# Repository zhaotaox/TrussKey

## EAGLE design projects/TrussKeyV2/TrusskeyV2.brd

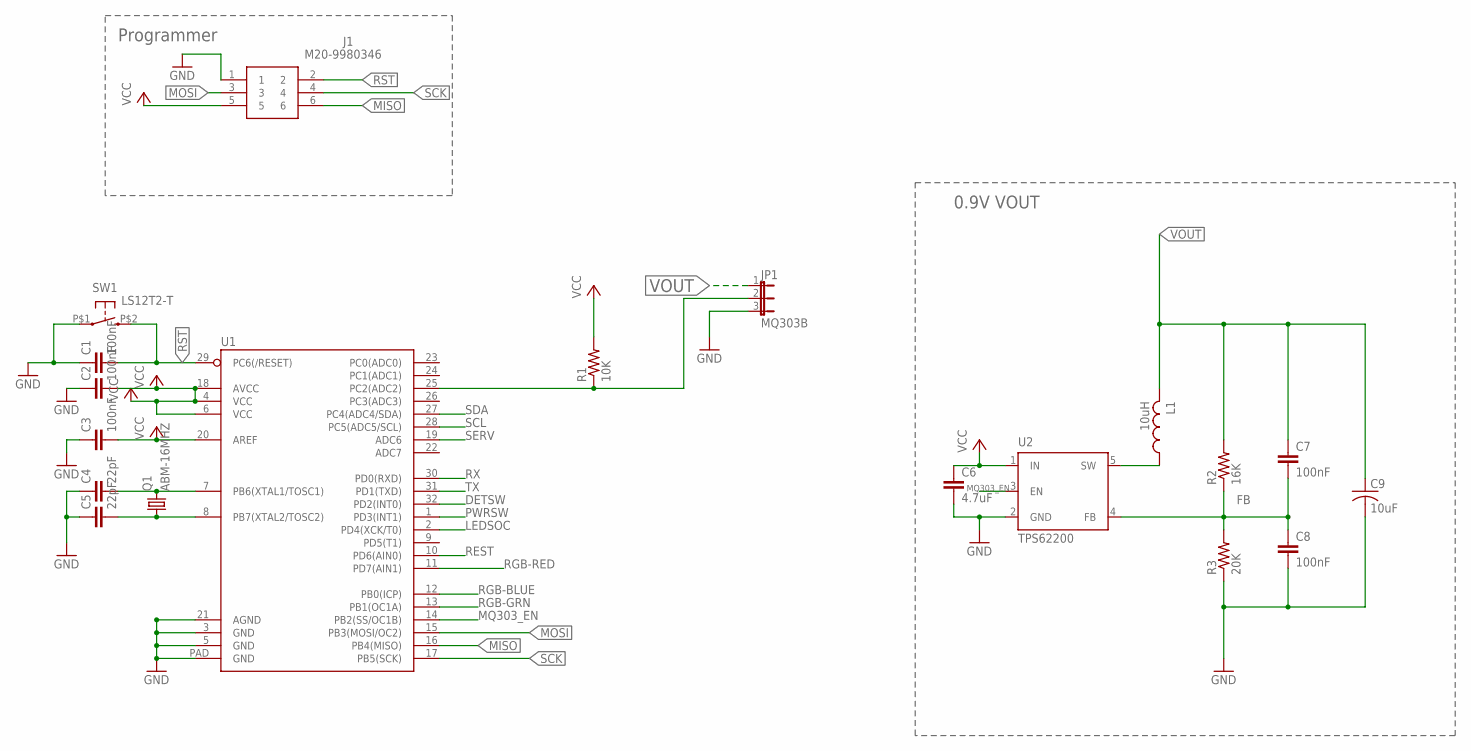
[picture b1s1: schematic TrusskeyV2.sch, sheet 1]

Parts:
C1, C2, C3: 100nF; C0603
C4, C5: 22pF; C0603
C6: 4.7uF; C0402
C7, C8: 100nF; C0402
C9: 10uF; C0805K
J1: M20-9980346; HDRV6W64P254_2X3_762X508X868P
JP1: MQ303B; JP2
L1: 10uH; L2825P
Q1: ABM-16MHZ
R1: 10K; R0402
R2: 16K; R0402
R3: 20K; R0402
SW1: LS12T2-T
U1: ATMEGA328P_MLFMLF32; MLF32-PAD
U2: TPS62200

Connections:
DETSW: U1.32 (PD2(INT0)); also elsewhere on the board
FB: C7.2, C8.1, R2.1, R3.2, U2.4 (FB)
GND: C1.1, C2.1, C3.1, C4.1, C5.1, C6.2, C8.2, C9.2, J1.1, JP1.3, R3.1, SW1.P$1 (S1), U1.3 (GND), U1.5 (GND), U1.21 (AGND), U1.PAD (GND), U2.2 (GND); also elsewhere on the board
LEDSOC: U1.2 (PD4(XCK/T0))
MISO: J1.6, U1.16 (PB4(MISO))
MOSI: J1.3, U1.15 (PB3(MOSI/OC2))
MQ303_EN: U1.14 (PB2(SS/OC1B)), U2.3 (EN)
unnamed: C5.2, Q1.P$1 (1), U1.8 (PB7(XTAL2/TOSC2))
unnamed: C4.2, Q1.P$2 (2), U1.7 (PB6(XTAL1/TOSC1))
unnamed: JP1.2, R1.1, U1.25 (PC2(ADC2))
PWRSW: U1.1 (PD3(INT1)); also elsewhere on the board
REST: U1.10 (PD6(AIN0)); also elsewhere on the board
RGB-BLUE: U1.12 (PB0(ICP)); also elsewhere on the board
RGB-GRN: U1.13 (PB1(OC1A)); also elsewhere on the board
RGB-RED: U1.11 (PD7(AIN1)); also elsewhere on the board
RST: C1.2, J1.2, SW1.P$2 (S2), U1.29 (PC6(/RESET))
RX: U1.30 (PD0(RXD)); also elsewhere on the board
SCK: J1.4, U1.17 (PB5(SCK))
SCL: U1.28 (PC5(ADC5/SCL)); also elsewhere on the board
SDA: U1.27 (PC4(ADC4/SDA)); also elsewhere on the board
SERV: U1.19 (ADC6); also elsewhere on the board
SW: L1.1, U2.5 (SW)
TX: U1.31 (PD1(TXD)); also elsewhere on the board
VCC: C2.2, C3.2, C6.1, J1.5, R1.2, U1.4 (VCC), U1.6 (VCC), U1.18 (AVCC), U1.20 (AREF), U2.1 (IN); also elsewhere on the board
VOUT: C7.1, C9.1, JP1.1, L1.2, R2.2

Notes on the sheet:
0.9V VOUT
Programmer

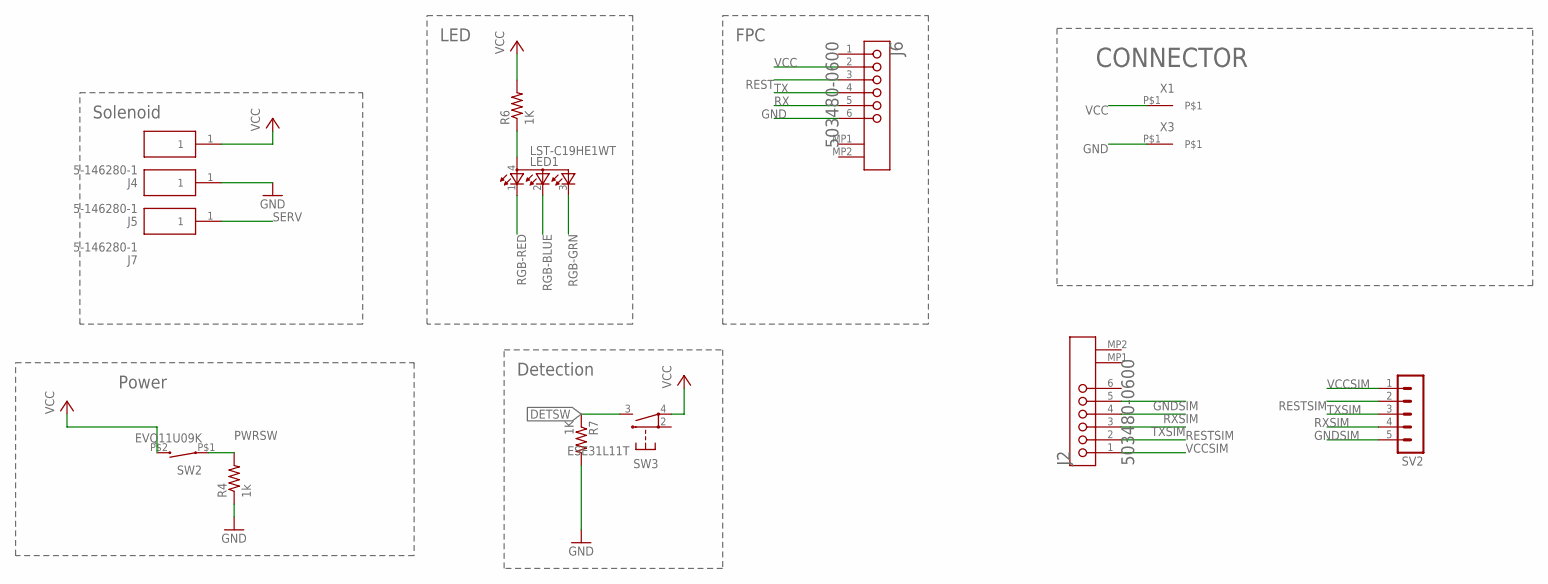
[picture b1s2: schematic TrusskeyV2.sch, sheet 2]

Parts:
J2, J6: MOLEX_503480-0600MOLEX_503480-0600_0_0; MOLEX_503480-0600_0
J4, J5, J7: 5-146280-1; HDRV1W67P0X254_1X1_213X234X821
LED1: LST-C19HE1WT
R4: 1k; R0402
R6, R7: 1K; R0402
SV2: MA05-1
SW2: EVQ11U09K; EVQ11U-09K
SW3: ESE31L11T; SWITCH
X1, X3: CON-1PIN

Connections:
DETSW: R7.1, SW3.3 (1); also elsewhere on the board
GND: J5.1, J6.6, R4.1, R7.2, X3.P$1; also elsewhere on the board
GNDSIM: J2.5, SV2.5
unnamed: LED1.4 (A), R6.1
PWRSW: R4.2, SW2.P$1 (1); also elsewhere on the board
REST: J6.3; also elsewhere on the board
RESTSIM: J2.2, SV2.2
RGB-BLUE: LED1.2 (CGREEN); also elsewhere on the board
RGB-GRN: LED1.3 (CBLUE); also elsewhere on the board
RGB-RED: LED1.1 (CRED); also elsewhere on the board
RX: J6.5; also elsewhere on the board
RXSIM: J2.4, SV2.4
SERV: J7.1; also elsewhere on the board
TX: J6.4; also elsewhere on the board
TXSIM: J2.3, SV2.3
VCC: J4.1, J6.2, R6.2, SW2.P$2 (2), SW3.4 (C3), X1.P$1; also elsewhere on the board
VCCSIM: J2.1, SV2.1

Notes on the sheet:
Solenoid
Power
LED
FPC
Detection
CONNECTOR

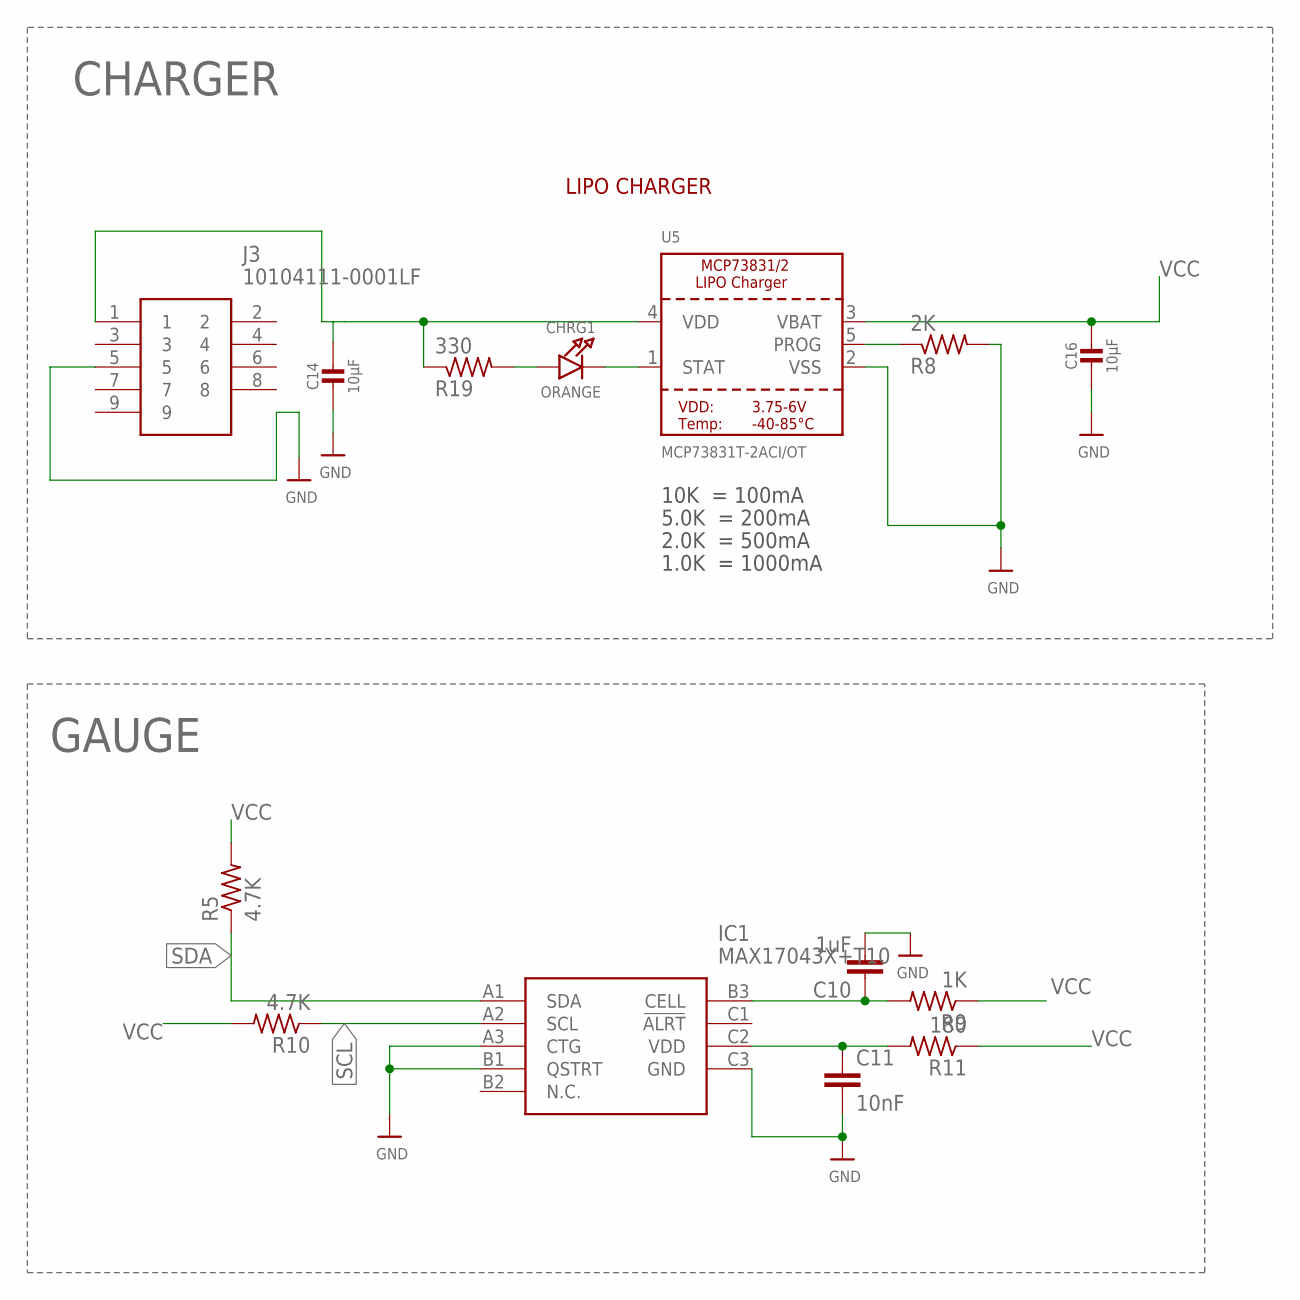
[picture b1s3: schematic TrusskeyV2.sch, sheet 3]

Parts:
C10: 1uF; C0603
C11: 10nF; C0603
C14, C16: 10µF; 0805-NO
CHRG1: ORANGE; CHIPLED_0805_NOOUTLINE
IC1: MAX17043X+T10; BGA9C40P3X3_160X142X69
J3: 10104111-0001LF; 101041110001LF
R5, R10: 4.7K; R0402
R8: 2K; R0402
R9: 1K; R0402
R11: 180; R0402
R19: 330; R0402
U5: MCP73831T-2ACI/OT; SOT23-5

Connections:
GND: C10.2, C11.2, C14.2, C16.2, IC1.A3 (CTG), IC1.B1 (QSTRT), IC1.C3 (GND), J3.5, R8.2, U5.2 (VSS); also elsewhere on the board
unnamed: C11.1, IC1.C2 (VDD), R11.2
unnamed: C10.1, IC1.B3 (CELL), R9.2
unnamed: R8.1, U5.5 (PROG)
unnamed: CHRG1.A, R19.2
unnamed: CHRG1.C, U5.1 (STAT)
SCL: IC1.A2 (SCL), R10.1; also elsewhere on the board
SDA: IC1.A1 (SDA), R5.1; also elsewhere on the board
VBUS2: C14.1, J3.1, R19.1, U5.4 (VDD)
VCC: C16.1, R5.2, R9.1, R10.2, R11.1, U5.3 (VBAT); also elsewhere on the board

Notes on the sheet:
10K = 100mA
5.0K = 200mA
2.0K = 500mA
1.0K = 1000mA
LIPO CHARGER
CHARGER
GAUGE

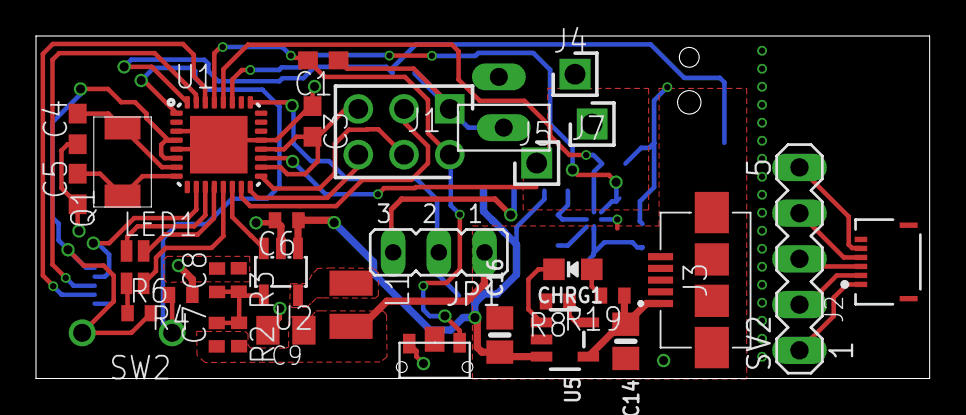
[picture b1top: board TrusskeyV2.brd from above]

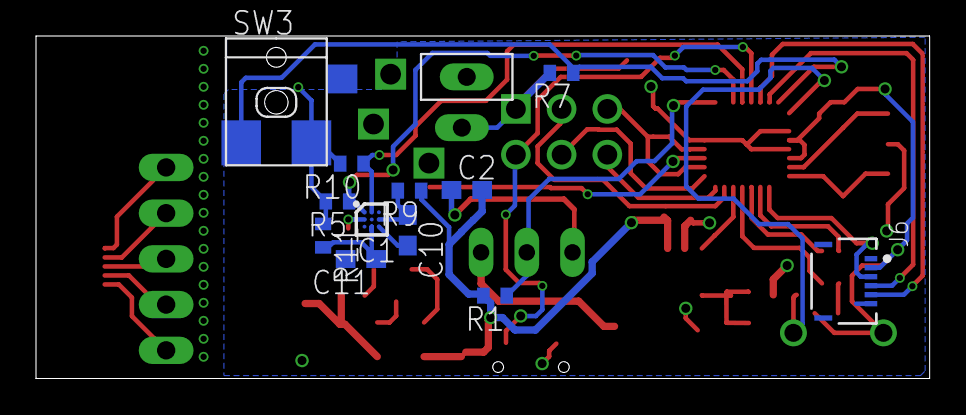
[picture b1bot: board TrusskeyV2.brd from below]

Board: 4 copper layers, 49.6 x 19.0 mm, 47 parts (13 on the bottom side), 36 nets.

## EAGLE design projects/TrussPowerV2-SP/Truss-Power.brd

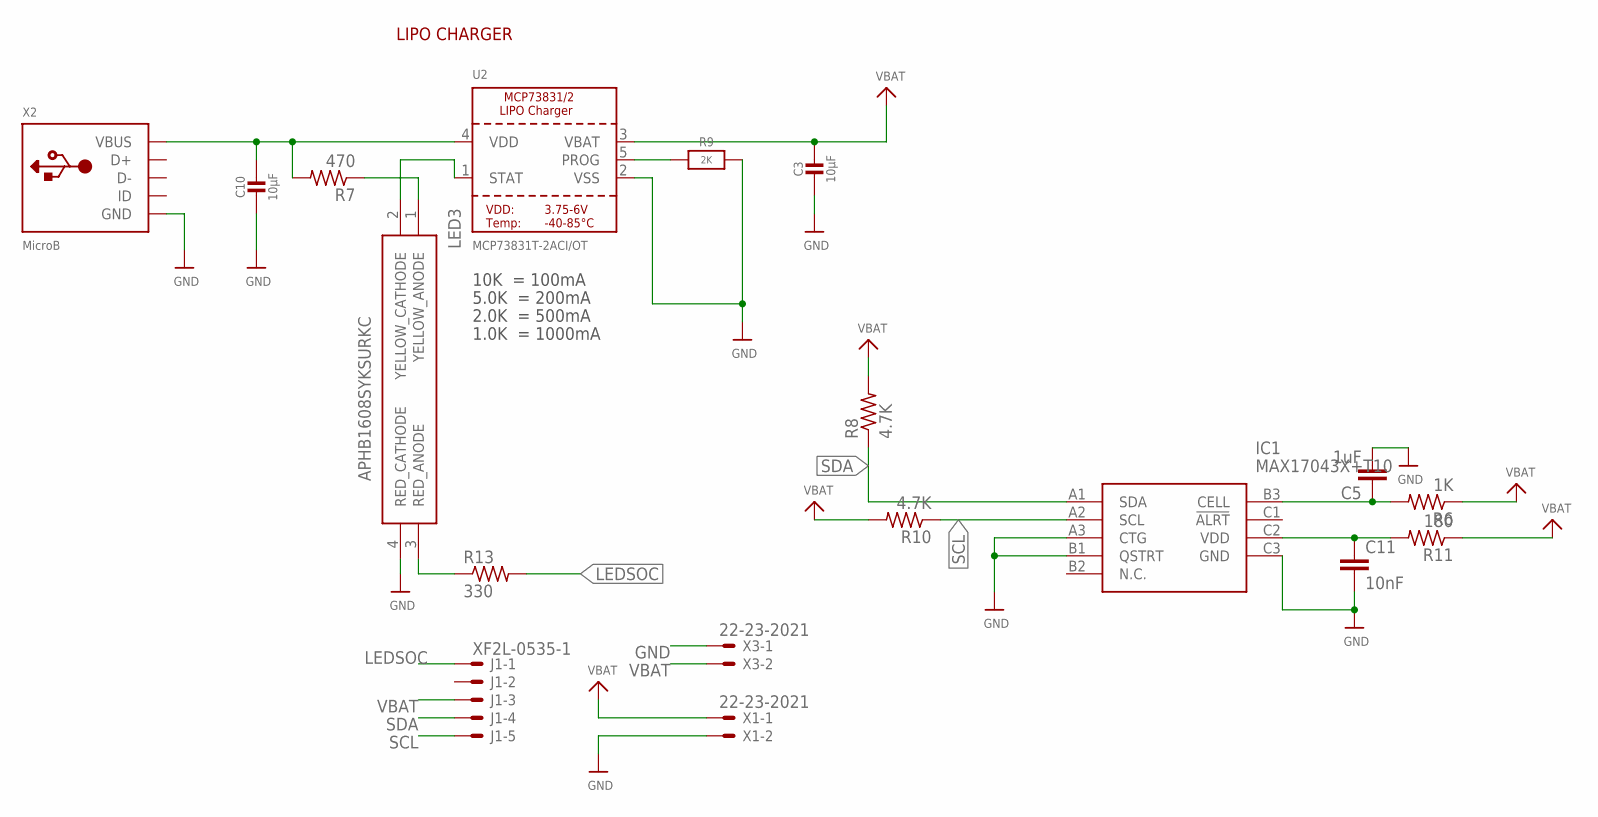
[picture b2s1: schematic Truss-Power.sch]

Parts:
C3, C10: 10µF; 0805-NO
C5: 1uF; C0603
C11: 10nF; C0603
IC1: MAX17043X+T10; BGA9C40P3X3_160X142X69
J1: XF2L-0535-1
LED3: APHB1608SYKSURKC; APHB1608ZGSURKC
R6: 1K; R0402
R7: 470; R0402
R8, R10: 4.7K; R0402
R9: 2K; 0805-NO
R11: 180; R0402
R13: 330; R0402
U2: MCP73831T-2ACI/OT; SOT23-5
X1, X3: 22-23-2021
X2: MicroB; 4UCONN_20329

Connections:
GND: C3.2, C5.2, C10.2, C11.2, IC1.A3 (CTG), IC1.B1 (QSTRT), IC1.C3 (GND), LED3.4 (RED_CATHODE), R9.2, U2.2 (VSS), X1.2, X2.BASE@1 (GND), X2.BASE@2 (GND), X2.GND, X2.SPRT@1 (GND), X2.SPRT@2 (GND), X2.SPRT@3 (GND), X2.SPRT@4 (GND), X3.1
LEDSOC: J1.1 (MSV), R13.2
unnamed: C5.1, IC1.B3 (CELL), R6.2
unnamed: C11.1, IC1.C2 (VDD), R11.2
unnamed: LED3.1 (YELLOW_ANODE), R7.1
unnamed: LED3.2 (YELLOW_CATHODE), U2.1 (STAT)
unnamed: LED3.3 (RED_ANODE), R13.1
unnamed: R9.1, U2.5 (PROG)
SCL: IC1.A2 (SCL), J1.5 (MS), R10.1
SDA: IC1.A1 (SDA), J1.4 (MS), R8.1
VBAT: C3.1, J1.3 (MS), R6.1, R8.2, R10.2, R11.1, U2.3 (VBAT), X1.1, X3.2
VBUS: C10.1, R7.2, U2.4 (VDD), X2.VBUS

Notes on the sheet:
10K = 100mA
5.0K = 200mA
2.0K = 500mA
1.0K = 1000mA
LIPO CHARGER

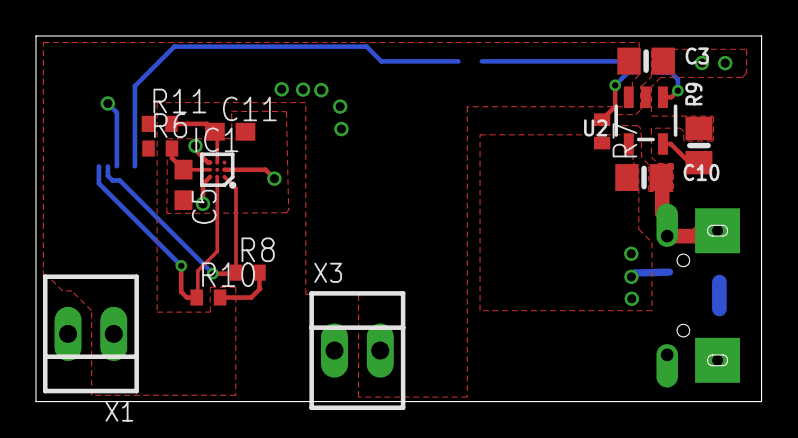
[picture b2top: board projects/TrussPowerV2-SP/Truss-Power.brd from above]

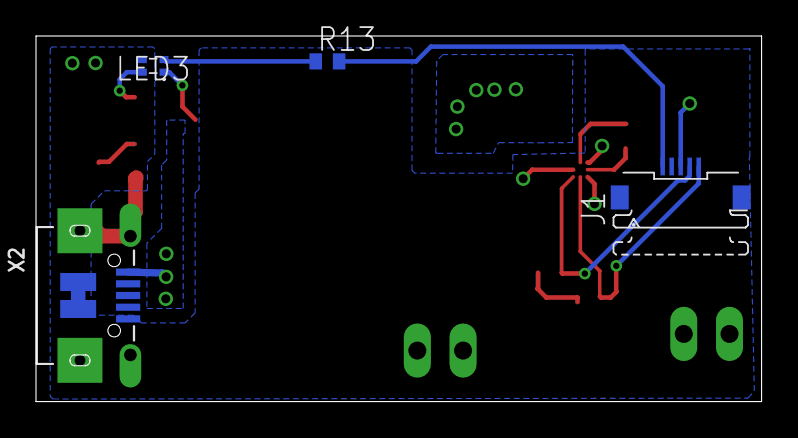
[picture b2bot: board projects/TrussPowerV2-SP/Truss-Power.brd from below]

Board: 2 copper layers, 40.3 x 20.3 mm, 18 parts (4 on the bottom side), 12 nets.

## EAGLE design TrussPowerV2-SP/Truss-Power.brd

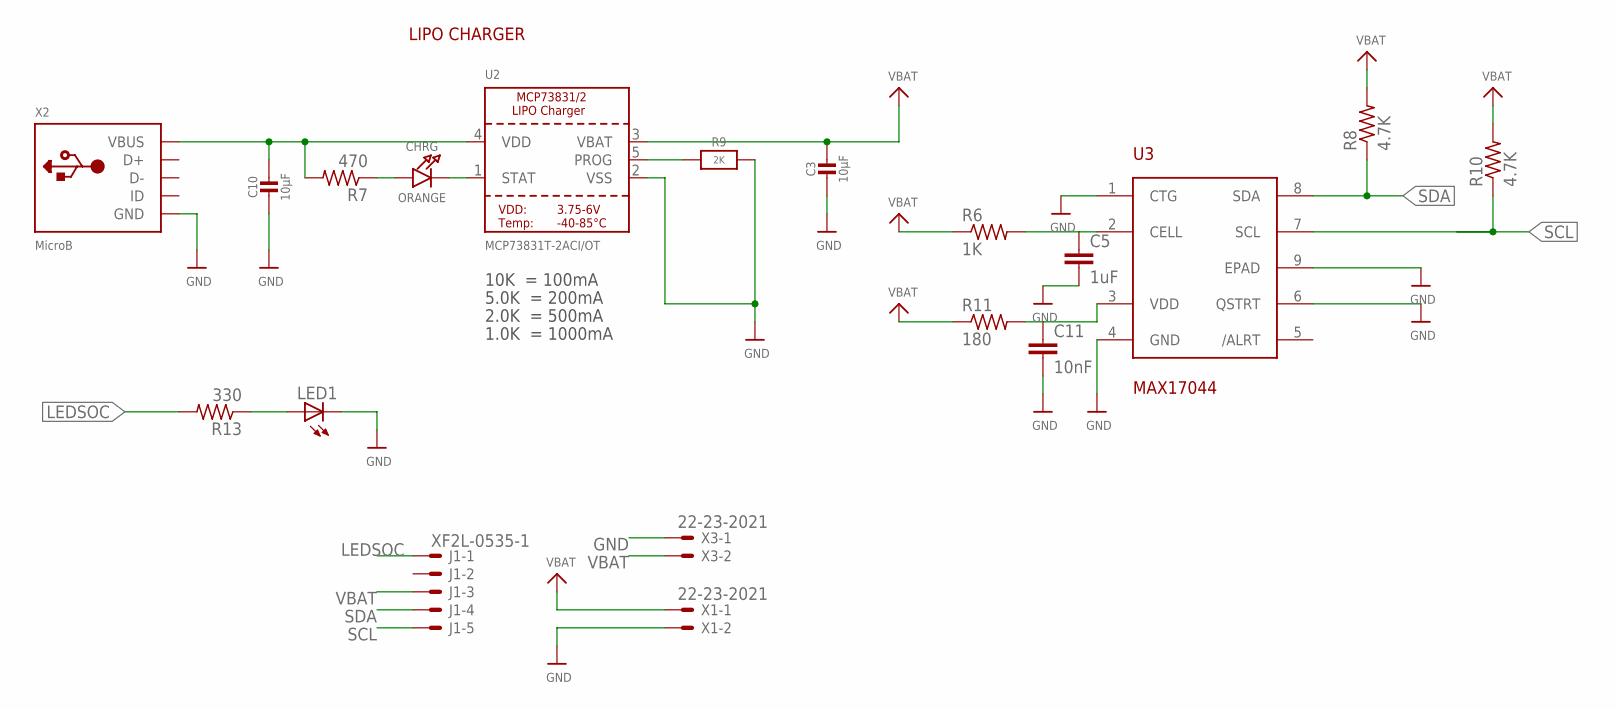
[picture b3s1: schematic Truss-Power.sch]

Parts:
C3, C10: 10µF; 0805-NO
C5: 1uF; C0603
C11: 10nF; C0603
CHRG: ORANGE; CHIPLED_0805_NOOUTLINE
J1: XF2L-0535-1
LED1: LEDCHIP-LED0603; CHIP-LED0603
R6: 1K; R0402
R7: 470; R0402
R8, R10: 4.7K; R0402
R9: 2K; 0805-NO
R11: 180; R0402
R13: 330; R0402
U2: MCP73831T-2ACI/OT; SOT23-5
U3: MAX17044; TDFN
X1, X3: 22-23-2021
X2: MicroB; 4UCONN_20329

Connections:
GND: C3.2, C5.2, C10.2, C11.2, LED1.C, R9.2, U2.2 (VSS), U3.1 (CTG), U3.4 (GND), U3.6 (QSTRT), U3.9 (EPAD), X1.2, X2.BASE@1 (GND), X2.BASE@2 (GND), X2.GND, X2.SPRT@1 (GND), X2.SPRT@2 (GND), X2.SPRT@3 (GND), X2.SPRT@4 (GND), X3.1
LEDSOC: J1.1 (MSV), R13.2
unnamed: C5.1, R6.2, U3.2 (CELL)
unnamed: C11.1, R11.2, U3.3 (VDD)
unnamed: LED1.A, R13.1
unnamed: CHRG.A, R7.1
unnamed: CHRG.C, U2.1 (STAT)
unnamed: R9.1, U2.5 (PROG)
SCL: J1.5 (MS), R10.1, U3.7 (SCL)
SDA: J1.4 (MS), R8.1, U3.8 (SDA)
VBAT: C3.1, J1.3 (MS), R6.1, R8.2, R10.2, R11.1, U2.3 (VBAT), X1.1, X3.2
VBUS: C10.1, R7.2, U2.4 (VDD), X2.VBUS

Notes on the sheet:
10K = 100mA
5.0K = 200mA
2.0K = 500mA
1.0K = 1000mA
LIPO CHARGER

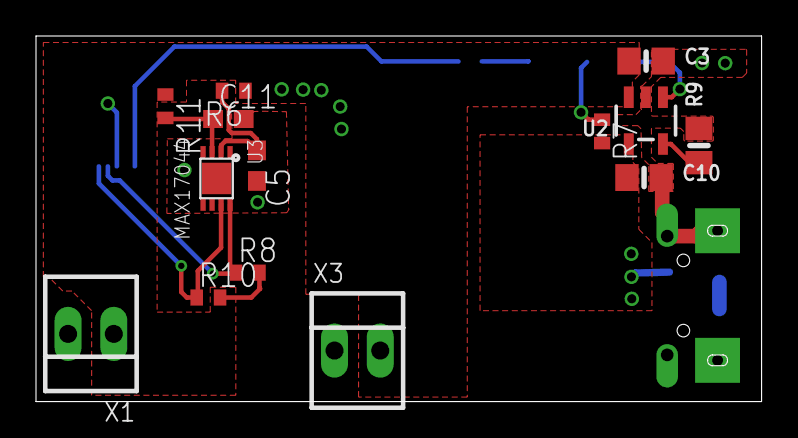
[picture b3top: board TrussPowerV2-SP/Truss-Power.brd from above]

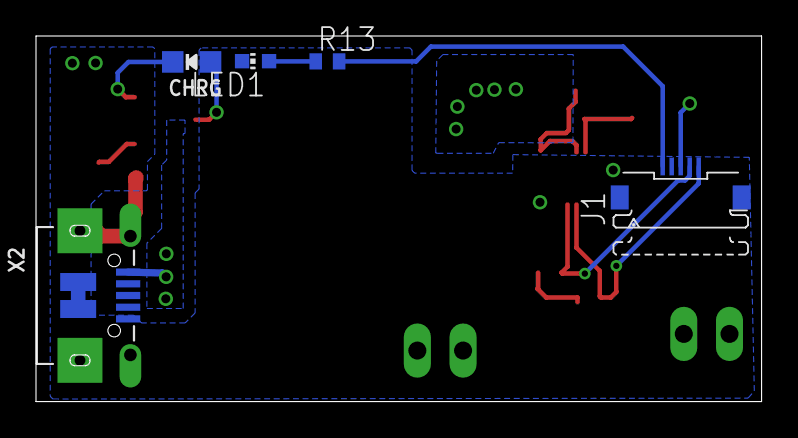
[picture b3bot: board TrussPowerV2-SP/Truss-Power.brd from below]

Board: 2 copper layers, 40.3 x 20.3 mm, 19 parts (5 on the bottom side), 12 nets.

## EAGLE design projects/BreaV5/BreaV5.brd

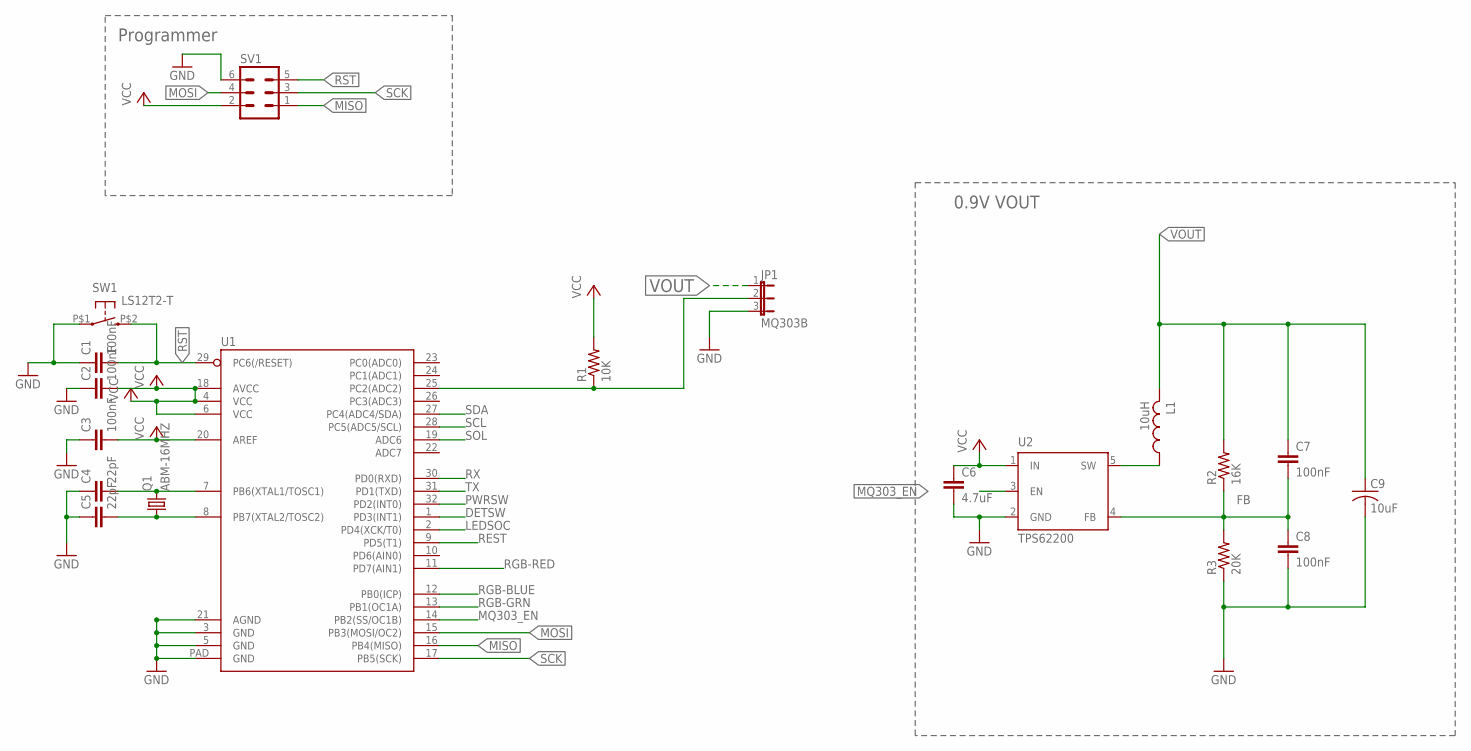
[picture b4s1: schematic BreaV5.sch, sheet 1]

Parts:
C1, C2, C3: 100nF; C0603
C4, C5: 22pF; C0603
C6: 4.7uF; C0402
C7, C8: 100nF; C0402
C9: 10uF; C0805K
JP1: MQ303B; JP2
L1: 10uH; L2825P
Q1: ABM-16MHZ
R1: 10K; R0402
R2: 16K; R0402
R3: 20K; R0402
SV1: MA03-2
SW1: LS12T2-T
U1: ATMEGA328P_MLFMLF32; MLF32-PAD
U2: TPS62200

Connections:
DETSW: U1.1 (PD3(INT1)); also elsewhere on the board
FB: C7.2, C8.1, R2.1, R3.2, U2.4 (FB)
GND: C1.1, C2.1, C3.1, C4.1, C5.1, C6.2, C8.2, C9.2, JP1.3, R3.1, SV1.6 (MISO), SW1.P$1 (S1), U1.3 (GND), U1.5 (GND), U1.21 (AGND), U1.PAD (GND), U2.2 (GND); also elsewhere on the board
LEDSOC: U1.2 (PD4(XCK/T0)); also elsewhere on the board
MISO: SV1.1, U1.16 (PB4(MISO))
MOSI: SV1.4, U1.15 (PB3(MOSI/OC2))
MQ303_EN: U1.14 (PB2(SS/OC1B)), U2.3 (EN)
unnamed: C5.2, Q1.P$1 (1), U1.8 (PB7(XTAL2/TOSC2))
unnamed: C4.2, Q1.P$2 (2), U1.7 (PB6(XTAL1/TOSC1))
unnamed: JP1.2, R1.1, U1.25 (PC2(ADC2))
PWRSW: U1.32 (PD2(INT0)); also elsewhere on the board
REST: U1.9 (PD5(T1)); also elsewhere on the board
RGB-BLUE: U1.12 (PB0(ICP)); also elsewhere on the board
RGB-GRN: U1.13 (PB1(OC1A)); also elsewhere on the board
RGB-RED: U1.11 (PD7(AIN1)); also elsewhere on the board
RST: C1.2, SV1.5 (VTG), SW1.P$2 (S2), U1.29 (PC6(/RESET))
RX: U1.30 (PD0(RXD)); also elsewhere on the board
SCK: SV1.3, U1.17 (PB5(SCK))
SCL: U1.28 (PC5(ADC5/SCL)); also elsewhere on the board
SDA: U1.27 (PC4(ADC4/SDA)); also elsewhere on the board
SOL: U1.19 (ADC6); also elsewhere on the board
SW: L1.1, U2.5 (SW)
TX: U1.31 (PD1(TXD)); also elsewhere on the board
VCC: C2.2, C3.2, C6.1, R1.2, SV1.2, U1.4 (VCC), U1.6 (VCC), U1.18 (AVCC), U1.20 (AREF), U2.1 (IN); also elsewhere on the board
VOUT: C7.1, C9.1, JP1.1, L1.2, R2.2

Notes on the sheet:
0.9V VOUT
Programmer

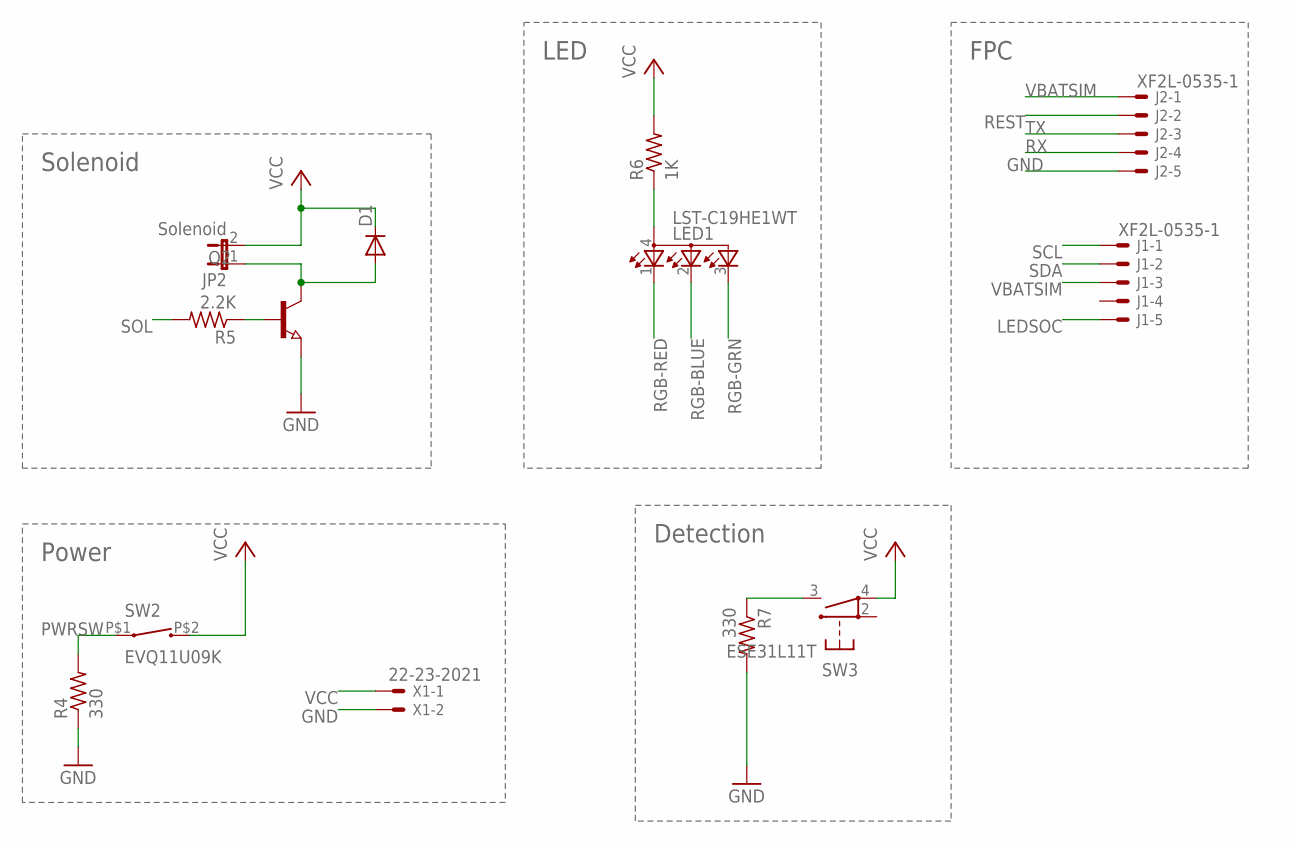
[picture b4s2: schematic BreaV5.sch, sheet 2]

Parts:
D1: DIODE-SOD123; SOD123
J1, J2: XF2L-0535-1
JP2: Solenoid; JP1
LED1: LST-C19HE1WT
Q2: NPN-TRANSISTOR_SOT23; SOT23
R4, R7: 330; R0402
R5: 2.2K; R0402
R6: 1K; R0402
SW2: EVQ11U09K; EVQ11U-09K
SW3: ESE31L11T; SWITCH
X1: 22-23-2021

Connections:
DETSW: R7.1, SW3.3 (1); also elsewhere on the board
GND: J2.5 (MS), Q2.2 (E), R4.1, R7.2, X1.2; also elsewhere on the board
LEDSOC: J1.5 (MS); also elsewhere on the board
unnamed: LED1.4 (A), R6.1
unnamed: D1.A, JP2.1, Q2.3 (C)
unnamed: Q2.1 (B), R5.1
PWRSW: R4.2, SW2.P$1 (1); also elsewhere on the board
REST: J2.2 (MS); also elsewhere on the board
RGB-BLUE: LED1.2 (CGREEN); also elsewhere on the board
RGB-GRN: LED1.3 (CBLUE); also elsewhere on the board
RGB-RED: LED1.1 (CRED); also elsewhere on the board
RX: J2.4 (MS); also elsewhere on the board
SCL: J1.1 (MSV); also elsewhere on the board
SDA: J1.2 (MS); also elsewhere on the board
SOL: R5.2; also elsewhere on the board
TX: J2.3 (MS); also elsewhere on the board
VBATSIM: J1.3 (MS), J2.1 (MSV)
VCC: D1.C, JP2.2, R6.2, SW2.P$2 (2), SW3.4 (C3), X1.1; also elsewhere on the board

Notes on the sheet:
Solenoid
Power
LED
FPC
Detection

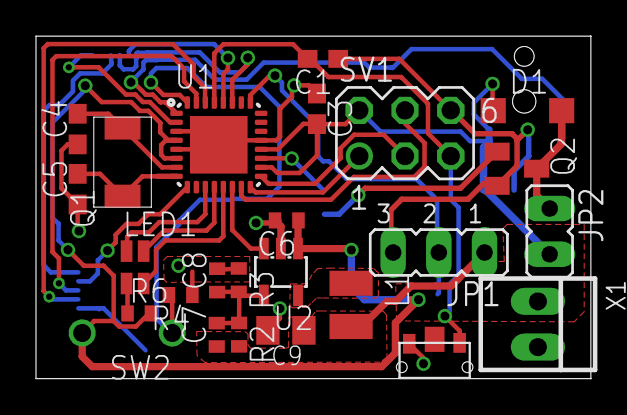
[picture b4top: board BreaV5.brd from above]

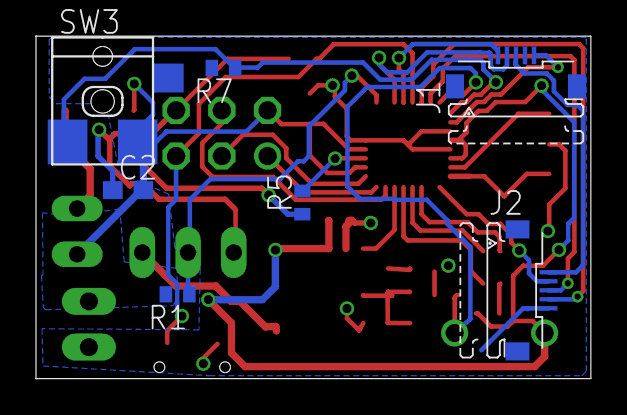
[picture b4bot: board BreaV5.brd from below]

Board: 2 copper layers, 30.8 x 19.0 mm, 32 parts (7 on the bottom side), 29 nets.

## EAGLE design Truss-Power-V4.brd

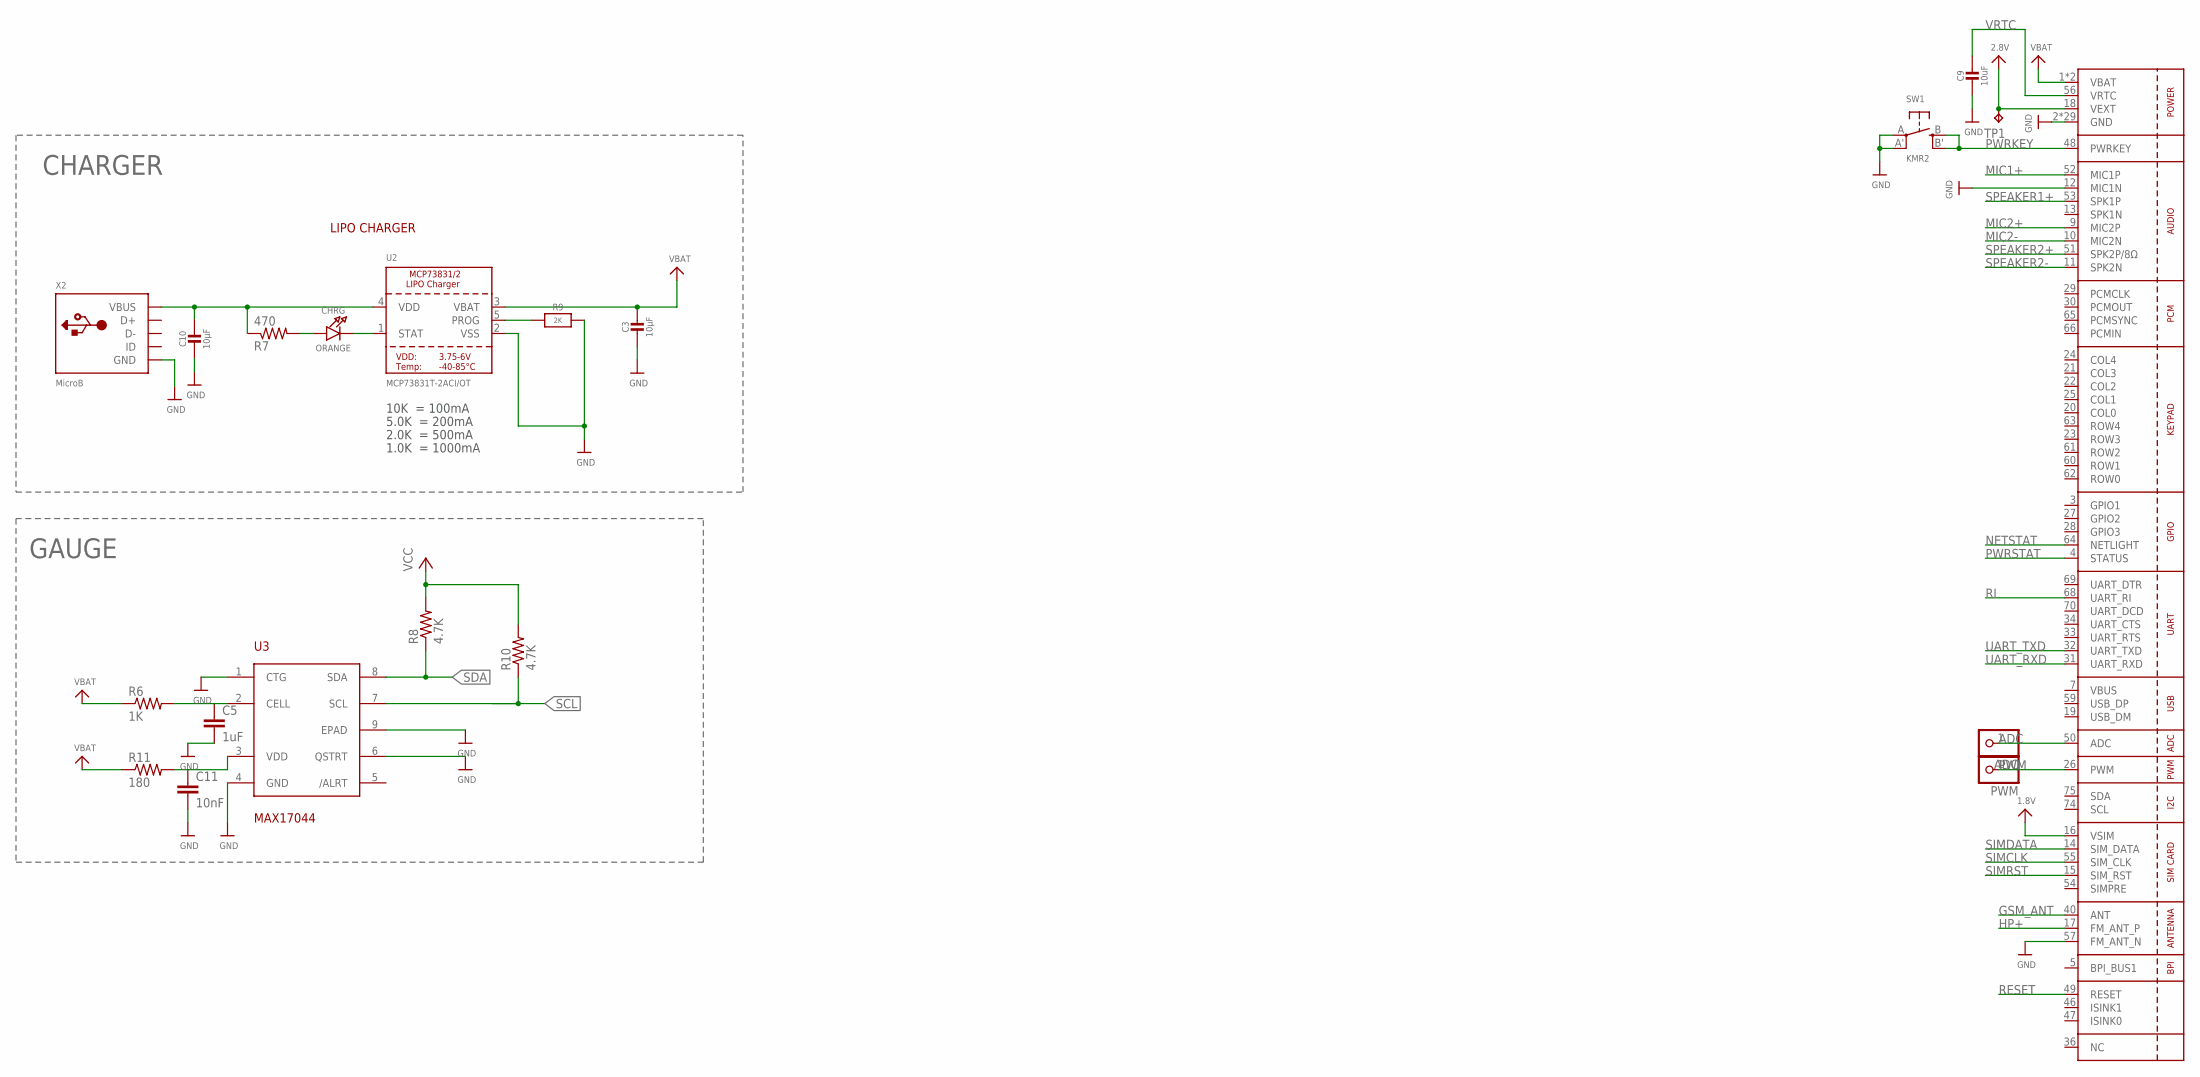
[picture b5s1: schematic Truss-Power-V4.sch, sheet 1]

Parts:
ADC: PINHD-1X1CB; 1X01-CLEANBIG
C3, C10: 10µF; 0805-NO
C5: 1uF; C0603
C9: 10uF; 0805-NO
C11: 10nF; C0603
CHRG: ORANGE; CHIPLED_0805_NOOUTLINE
PWM: PINHD-1X1CB; 1X01-CLEANBIG
R6: 1K; R0402
R7: 470; R0402
R8, R10: 4.7K; R0402
R9: 2K; 0805-NO
R11: 180; R0402
SW1: KMR2; BTN_KMR2_4.6X2.8
TP1: TPTP11R; TP11R
U2: MCP73831T-2ACI/OT; SOT23-5
U3: MAX17044; TDFN
U4: SIM800H/L; SIM800L
X2: MicroB; 4UCONN_20329

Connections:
1.8V: U4.16 (VSIM)
2.8V: TP1.TP, U4.18 (VEXT)
ADC: ADC.1, U4.50 (ADC)
GND: C3.2, C5.2, C9.2, C10.2, C11.2, R9.2, SW1.A, SW1.A' (P1), U2.2 (VSS), U3.1 (CTG), U3.4 (GND), U3.6 (QSTRT), U3.9 (EPAD), U4.2 (GND), U4.6 (GND), U4.8 (GND), U4.12 (MIC1N), U4.35 (GND), U4.37 (GND), U4.38 (GND), U4.39 (GND), U4.41 (GND), U4.43 (GND), U4.44 (GND), U4.45 (GND), U4.57 (FM_ANT_N), U4.58 (GND), U4.67 (GND), U4.71 (GND), U4.72 (GND), U4.73 (GND), U4.76 (GND), U4.77 (GND), U4.78 (GND), U4.79 (GND), U4.80 (GND), U4.81 (GND), U4.82 (GND), U4.83 (GND), U4.84 (GND), U4.85 (GND), U4.86 (GND), U4.87 (GND), U4.88 (GND), X2.BASE@1 (GND), X2.BASE@2 (GND), X2.GND, X2.SPRT@1 (GND), X2.SPRT@2 (GND), X2.SPRT@3 (GND), X2.SPRT@4 (GND); also elsewhere on the board
GSM_ANT: U4.40 (ANT)
HP+: U4.17 (FM_ANT_P)
MIC1+: U4.52 (MIC1P)
MIC2+: U4.9 (MIC2P)
MIC2-: U4.10 (MIC2N)
unnamed: C5.1, R6.2, U3.2 (CELL)
unnamed: C11.1, R11.2, U3.3 (VDD)
unnamed: CHRG.A, R7.2
unnamed: CHRG.C, U2.1 (STAT)
unnamed: R9.1, U2.5 (PROG)
NETSTAT: U4.64 (NETLIGHT)
PWM: PWM.1, U4.26 (PWM)
PWRKEY: SW1.B (S), SW1.B' (S1), U4.48 (PWRKEY)
PWRSTAT: U4.4 (STATUS)
RESET: U4.49 (RESET)
RI: U4.68 (UART_RI)
SCL: R10.1, U3.7 (SCL); also elsewhere on the board
SDA: R8.1, U3.8 (SDA); also elsewhere on the board
SIMCLK: U4.55 (SIM_CLK)
SIMDATA: U4.14 (SIM_DATA)
SIMRST: U4.15 (SIM_RST)
SPEAKER1+: U4.53 (SPK1P)
SPEAKER2+: U4.51 (SPK2P/8Ω)
SPEAKER2-: U4.11 (SPK2N)
UART_RXD: U4.31 (UART_RXD)
UART_TXD: U4.32 (UART_TXD)
VBAT: C3.1, R6.1, R8.2, R10.2, R11.1, U2.3 (VBAT), U4.1 (VBAT), U4.42 (VBAT); also elsewhere on the board
VBUS: C10.1, R7.1, U2.4 (VDD), U4.7 (VBUS), X2.VBUS
VRTC: C9.1, U4.56 (VRTC)

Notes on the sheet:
10K = 100mA
5.0K = 200mA
2.0K = 500mA
1.0K = 1000mA
LIPO CHARGER
CHARGER
GAUGE

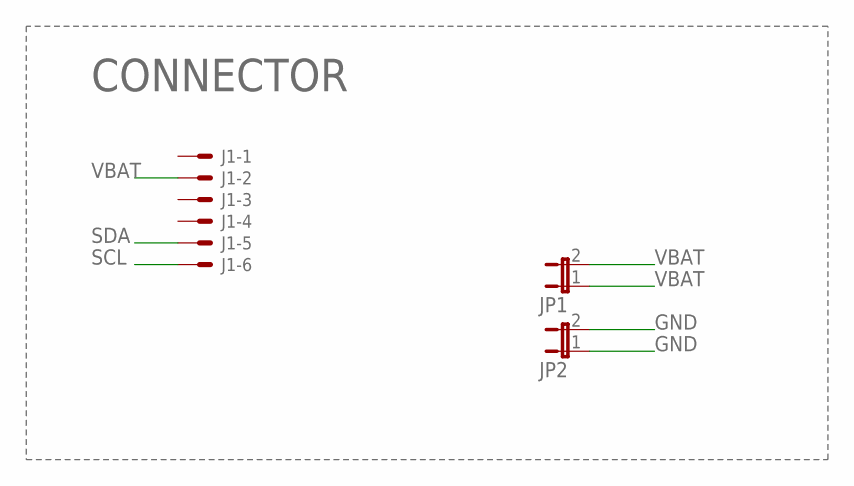
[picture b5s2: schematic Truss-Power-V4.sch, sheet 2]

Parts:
J1: XF2L-0625-1
JP1, JP2: JP1E; JP1

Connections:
GND: JP2.1, JP2.2; also elsewhere on the board
SCL: J1.6; also elsewhere on the board
SDA: J1.5; also elsewhere on the board
VBAT: J1.2, JP1.1, JP1.2; also elsewhere on the board

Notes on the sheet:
CONNECTOR

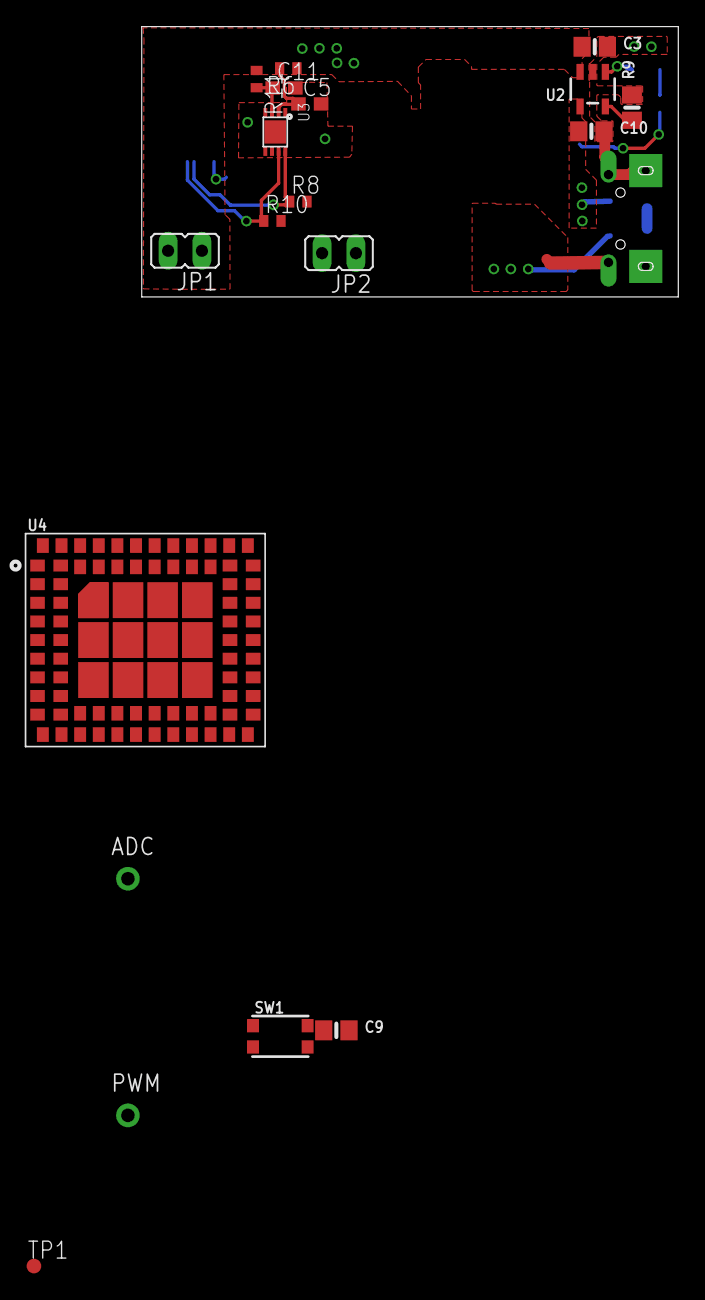
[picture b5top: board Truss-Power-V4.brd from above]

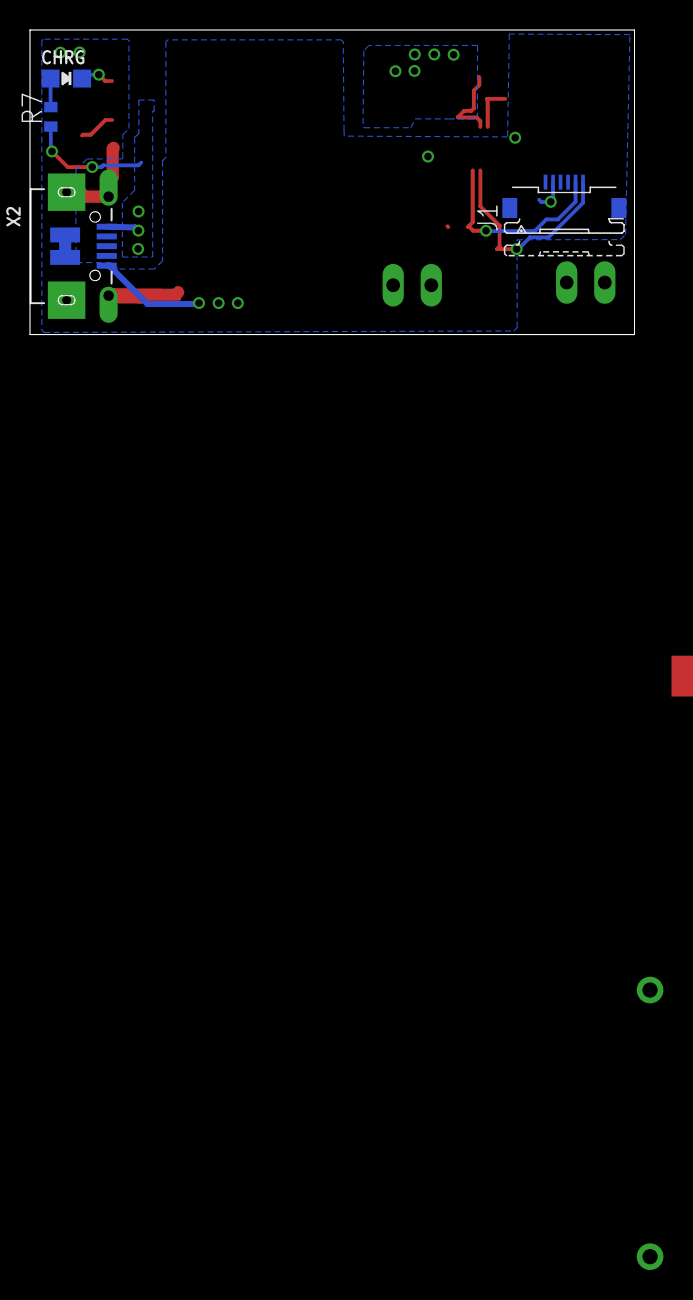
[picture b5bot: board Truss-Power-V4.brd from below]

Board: 2 copper layers, 40.3 x 20.3 mm, 23 parts (4 on the bottom side), 15 nets.

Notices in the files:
parts and their libraries:
SparkFun-DigitalIC: Licensing: Creative Commons ShareAlike 4.0 International - https://creativecommons.org/licenses/by-sa/4.0
microbuilder: This work is placed in the public domain, and may be freely used for commercial and non-commercial work with the following conditions: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
